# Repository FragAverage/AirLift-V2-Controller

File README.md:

# AirLift V2 Controller

The **AirLift V2 Controller** is a man-in-the-middle controller that sits inline
between an **AirLift V2 Controller controller** and the **air-management
manifold**. It **decodes the proprietary 9600-baud LIN-wired protocol**
in both directions, **rewrites frames if required** so a phone or the vehicle can
drive presets and manual air-up/down without ever desyncing the OEM Controller,
and **reads the vehicle CAN bus** for ignition sensing, lock/unlock triggers (like key fob)
and a live pressure broadcast. Everything is configured from a phone over
**Wi-Fi** — no laptop or serial cable needed in the car.

It runs on the same **ESP32 DevKit V1 (WROOM-32)** PCB as the
[MFSW Controller](https://forbes-automotive.com/products/lin-mfsw-controller),
under the Arduino framework, using both hardware UARTs for the two LIN sides and
the ESP32 **TWAI** peripheral for CAN.

> The firmware acts as a relay and only intercepts
> the manifold bus transiently while a command is queued — control always
> returns to the controller automatically.

---

## Features at a Glance

| Feature | Detail |
|---|---|
| Dual-LIN | Dual LIN channels for Controller (UART1) and manifold (UART2) in dedicated FreeRTOS tasks |
| AirLift Decoder | Decodes every observed frame: FA/F3 polls & replies, the 17-byte status frame, and the 14-byte format-B pressure broadcast |
| Rewrite-in-flight injection | Presets, manual buttons, mode-switch — with verified checksums; the manifold only ever sees one continuous master, so it can't desync |
| Preset editor | Each of 8 presets stored as a `(frontPsi, rearPsi)` in EEPROM, plus a live **Learn** capture from the Controller to allow the user to learn each preset |
| Auto air-out | On ignition loss, broadcast the configured "air-down" target (preset or manual), hold, then turn off manifold power |
| CAN / TWAI | Powertrain quiet-bus ignition detection **or** Comfort-CAN lock/unlock triggers, plus a ~10 Hz pressure broadcast onto the selected bus |
| SavvyCAN GVRET | Capture/inject CAN over Wi-Fi (TCP 23) or USB serial for reverse-engineering |
| Lock/unlock air actions | A double fob-unlock airs the car up; a double fob-lock airs it down (both individually selectable) |
| High-side driver | Powers the controller whenever the vehicle is awake, with configurable CAN silence / min-FPS thresholds |
| Slave display | ~10 Hz ESP-NOW broadcast of pressures / preset / air state to a cluster-mounted CYD display (`SlaveDisplay/`) |
| Wi-Fi UI | Overview, Presets, Settings, Diagnostics, OTA |
| Power management | Auto Wi-Fi-off + CPU reduction 1 minute after the last client disconnects; a fresh CAN burst wakes it back up |
| OTA updates | Flash new firmware from the browser over Wi-Fi |
| EEPROM storage | All settings and presets stored to ESP32 Preferences |

---

### Purchase

The controller runs on the same PCB as the LIN MFSW Controller, available here:
[LIN MFSW Controller — Forbes Automotive](https://forbes-automotive.com/products/lin-mfsw-controller)

---

## Compatibility

Designed for the **AirLift V2** controller + manifold pair that communicate over a
**9600-baud 8N1 LIN-transceiver bus**. The controller is the **bus master** (the
bus is silent when it is unplugged). Frame formats, button codes and checksums
in [`include/defs.h`](include/defs.h) were reverse-engineered from live Saleae
captures (see [`Documents/`](Documents/)) — treat them as a known-good baseline
and re-verify against your own hardware before relying on any injected output.

CAN frame IDs (Comfort fob, broadcast) are **VW PQ-specific** and configurable.

---

## Hardware Overview

### External Interfaces

| Function | Part / circuit |
| --- | --- |
| Controller LIN (LIN 1) | LIN transceiver on `Serial1`, 9600 8N1 — the controller is the master, this device relays it |
| Manifold LIN (LIN 2) | LIN transceiver on `Serial2`, 9600 8N1 — the manifold is the slave |
| CAN | ESP32 TWAI + transceiver (TJA1050 / SN65HVD230); 500 kbit/s Powertrain or 100 kbit/s Comfort |
| Ignition sense (aux) | Optional 12 V level input on the shared aux pin (GPIO 39, input-only) for instant ignition |
| High-side driver | Transistor output (OUTPUT1) supplies +12 V to the controller during ignition-off air-out (5A max.) |

### Pin Map

Defined in [`include/defs.h`](include/defs.h):

| Group | Signal | GPIO |
| --- | --- | --- |
| LIN 1 (Controller) | TX / RX | 17 / 16 |
| LIN 2 (manifold) | TX / RX | 23 / 22 |
| LIN transceivers | Wake / CS-EN | 18 / 19 |
| CAN / TWAI | RX / TX | 13 / 14 |
| Ignition sense | Aux input (input-only pin) | 39 |
| High-side driver | Controller +12 V ("PNP") | 21 |

UARTs are 9600 8N1; CAN is 500 kbit/s (Powertrain) or 100 kbit/s (Comfort).

### Main Connector

The device breaks out to a single 12-way **MX23A12NF1** connector (shared PCB
with the MFSW controller):

> Viewed into the mating face: the top row runs pin **1** (right) to pin **6**
> (left), and the bottom row runs pin **7** (right) to pin **12** (left).

| Pin | Signal | AirLift use |
| --- | --- | --- |
| 1 | `PWR_IN` | 12 V switched / ignition supply |
| 2 | `GND` | Ground |
| 3 | `LIN1` | Controller LIN bus |
| 4 | `LIN2` | Manifold LIN bus |
| 5 | `CHASSIS_CANH` | CAN high |
| 6 | `CHASSIS_CANL` | CAN low |
| 7 | `ANALOG_LIGHT_IN` | Optional ignition-sense input (aux) |
| 8 | `RA` | Unused (resistive output not populated) |
| 9 | `5V` | 5 V rail — typically not required |
| 10 | `OUTPUT1` | Controller +12 V high-side driver |
| 11 | — | Unused |
| 12 | — | Unused |

---

## Jumpers

The shared PCB carries three configuration jumpers:

### LIN1_MASTER

Master pull-up on **LIN 1** (the controller bus). The AirLift Controller provides
the bus master, so this jumper is normally **left off** on the adapter — fit it
only if bench-testing without the real Controller attached.

### LIN2_MASTER

Master pull-up on **LIN 2** (the manifold bus). Fit it if the adapter must
provide the master pull-up on the manifold side; remove it if the manifold
harness already supplies one.

### R_TERM1

The **CAN bus termination resistor**. If this is the only device on the CAN
network leave it fitted; if the vehicle bus is already terminated, remove it.

---

## How It Works

The two LIN sides and the CAN bus each run in dedicated FreeRTOS tasks. The
firmware never seizes the manifold bus outright — the real Controller keeps
polling at its own rate and the firmware simply **rewrites those
frames as they pass through**. Because the manifold only ever sees one
continuous, correctly framed master it can never desync.

```
Controller LIN (master)                Manifold LIN (slave)              Vehicle CAN
        │                                   ▲                              │
        ▼ ControllerToManifoldTask (core 1)   │ manifoldToControllerTask       ▼ ignitionTask (core 0)
 parse poll / button ────────────┐          │ (core 1)                pollCanRx()
        │                        │          │  parse status/pressure       │
   RESTING: byte relay ──────────┼──────────┘  RESTING: byte relay         ▼ switch(id):
        │                        │          ▲       │                 Comfort 0x291 → lock/unlock
   COMMAND: drop poll,           │          │       ▼                       │
   drive manifold ~20 Hz ────────┘   rewrite reply, credit-gated       air-up / air-down queue
        (transformControllerFrame)      relay back to Controller                │
                                                                            ▼ canBroadcastTick()
                                                                     8-byte pressure frame (~10 Hz)
```

### Resting vs. Command

- **Resting** (the default) is a real-time byte-for-byte relay in both
  directions. Both channels still parse a side-channel copy of the traffic, so
  pressures, mode and button state stay live without slowing the bus.
- **Command** (a queued web/CAN action) drops the Controller's messages and drives the manifold at the OEM's active ~20 Hz rate. 

### Air-up / Air-down Triggers

| Source | Action |
| --- | --- |
| Web UI preset / manual buttons | Queue a preset target or manual corner move |
| Ignition loss (`airOutOnIgnOff`) | Broadcast the configured air-down target, hold, drop Controller power |
| Comfort-CAN **double unlock** (`airUpOnFobDouble`) | Air up to the configured preset / PSI |
| Comfort-CAN **double lock** (`airDownOnFobDouble`) | Air down to the configured preset / PSI |

Manual-target moves are closed-loop: the firmware pulses the matching corner
button until the measured axle PSI reaches the target (within tolerance) or the
60s timeout expires.  This may need adjustment(!).

---

## LIN Protocol (Reverse-Engineered)

### Format A — FA-framed polls and replies

```
FA  <payload bytes>  F3
```

**Controller → Manifold (master polls)**

| Bytes                                          | Meaning                              |
|------------------------------------------------|--------------------------------------|
| `01 00 05`                                     | idle poll                            |
| `01 41 XX YY`                                  | MANUAL-mode button event, `YY = (0xC4 - XX) & 0xFF` |
| `01 14 40 00 00 00 B1`                         | PRESET-mode entry poll (state `0x40`, one-shot) |
| `01 14 43 00 00 00 AE`                         | PRESET-mode steady poll (state `0x43`) |
| `01 16 47 TL TR 0F TL TR CHK`                  | preset target broadcast; `TL`/`TR` = front/rear PSI × 2 |

**Manifold → Controller (slave replies)**

| Bytes              | Meaning                          |
|--------------------|----------------------------------|
| `10 F1 00 05`      | idle reply                       |
| `10 F1 04 01`      | reply, MANUAL mode               |
| `10 F1 01 04`      | reply, PRESET mode               |
| `10 0E 00 25 …`    | 17-byte status frame (see below) |

### Manual Button Codes (`01 41 XX YY`, payload[2])

Upper nibble = axle (5 = front, 6 = rear); lower nibble = one-hot bit per
(side, direction): bit0 = L-UP, bit1 = L-DOWN, bit2 = R-UP, bit3 = R-DOWN.

| Code | Button       |  | Code | Button         |
|------|--------------|--|------|----------------|
| 0x51 | FL_UP        |  | 0x61 | RL_UP          |
| 0x52 | FL_DOWN      |  | 0x62 | RL_DOWN        |
| 0x54 | FR_UP        |  | 0x64 | RR_UP          |
| 0x58 | FR_DOWN      |  | 0x68 | RR_DOWN        |
| 0x00 | release/idle |  | 0x80 | MODE_SWITCH (press+hold 1+5) |

Checksum: payload[3] = `(0xC4 - code) & 0xFF`.

### Format A — 17-byte status frame (Manifold → Controller)

```
FA 10 0E 00 MS  FL  RL  FR  RR  TANK  C8 00 00 00 33 00 CHK F3
```

- `payload[3]` = mode/compressor flags: bit5 (`0x20`) heartbeat, bit4 (`0x10`)
  poll-parity, bits0+2 (`0x05`) both set if the compressor is running.
- `payload[5..8]` = FL, RL, FR, RR raw PSI (× 1, **not** × 2).
- `payload[9]`    = tank raw PSI.
- `payload[16]`   = sum-checksum: `(0xFA + Σpayload[0..15] + chk) mod 256 == 0`.

### Format B — 14-byte pressure broadcast (idle-terminated, no FA/F3)

```
00 0A E6 7E   C8 00 4A 00   FL  FR  RL  RR  b12 b13
```

Pressure bytes are PSI × 2. Frame is terminated by ≥4 ms of bus silence
(`kFrameIdleMs`). Kept as a secondary pressure source; format-A status is
preferred when available.

> **Pressure Refresh Rate.** In resting mode pressures are parsed on
> *every* frame the manifold emits, so the on-device values are always as fresh
> as the bus allows. The dashboard now polls `/api/status` at 4 Hz (250 ms).
> The underlying rate is set by how often the manifold chooses
> to broadcast

---

## CAN / TWAI

- **Listen-only** by default; reset to NORMAL mode only when *CAN Broadcast* or
  SavvyCAN transmit is enabled, so the firmware never emits ACK/error bits onto
  a bus while just monitoring.
- Re-initialised in [`src/CAN.cpp`](src/CAN.cpp) (`canReinit()`) when the
  enable flag, ID or bus rate changes via `/api/settings`.

### CAN Source

Exactly one CAN bus is active at a time (a single TWAI controller can only run
at one bit-rate):

- **Powertrain CAN** (500 kbit/s, default) — quiet-bus / minimum-FPS ignition
  detection. Presence is decided by combined activity: silence longer than
  `canSilSec` (default 10 s) **and** frame rate below `canMinFps` (default 50) →
  ignition OFF.
- **Comfort CAN** (100 kbit/s) — parses lock/unlock. `pollCanRx()` feeds each
  frame to a simple `switch (frame.identifier)` case statement; the Comfort fob
  frame (`0x291`, byte 0 = `0x4B` unlock / `0x8B` lock) sets the lock state, and
  a **double** press within 5s queues the configured air-up (unlock) or
  air-down (lock) action.

### Lock/Unlock → Air-Up/Down 

```
Comfort frame 0x291 → canProcessFrame() switch → unlock/lock + double-press detect
                                              → comfortFobDoubleUnlock / …Lock flag
ignitionTask → sees flag → queueTarget(air-up | air-down) → manifold drive
```

### Pressure Broadcast (firmware → vehicle bus)

~10 Hz (`kCanBroadcastPeriodMs = 100`), user-configured 11-bit ID (default
`0x520`), DLC 8:

```
[0] FL PSI*2   [1] FR PSI*2   [2] RL PSI*2   [3] RR PSI*2   [4] Tank PSI*2
[5] flags: bit0 compOn | bit1 ignOn | bit2 intercept | bit3 passthru
          | bits4-5 mode (0=unknown,1=manual,2=preset)
[6] seq counter (free-running)   [7] reserved (0)
```

### Slave Display Broadcast (firmware → ESP-NOW)

A one-way ~10 Hz (`kEspNowPeriodMs = 100`) broadcast to `FF:FF:FF:FF:FF:FF` of
the 24-byte `AirLiftData` struct in `include/airlift_espnow.h` — the receiving
end is the cluster display in **`SlaveDisplay/`**. Broadcast means no pairing and
no knowledge of the display's MAC; nothing is ever received.

```
float fl, fr, rl, rr, tank   // PSI
uint8 preset                 // 1-8 active preset, 0 = none
uint8 status                 // 0 idle, 1 raising, 2 lowering, 3 no signal
```

The struct must stay **byte-identical** to `SlaveDisplay/include/airlift_espnow.h`
(a `static_assert` on both sides guards the size; the receiver can only check the
length, not the field layout).

Two things the LIN wire does not carry directly, so the firmware derives them:

- **Active preset** — the wire has no preset index, only the target pressures
  from `01 16 47`. Those are matched back against the configured/learned preset
  table, which is the same mapping the UI's preset list uses. No match, or not in
  PRESET mode, sends `0` and the display shows `---`.
- **Raising / lowering** — the compressor bit only says the pump is running
  (also true while it refills the tank). Direction comes from a button being held
  right now (ours or the handheld's), and otherwise from the trend of the corner
  pressures, which also covers preset moves where the manifold closed-loops with
  no button held at all.

Because ESP-NOW rides the Wi-Fi radio, the soft-AP channel is pinned to
`kEspNowChannel` (1) to match the display's fixed `ESPNOW_WIFI_CHANNEL`, and the
radio is held up while the broadcast is enabled **and** the ignition is on — see
Power Management below. Toggle in **Settings → Slave Display (ESP-NOW)**.

### SavvyCAN

Enable one setting in **Settings → SavvyCAN**:

- **Wi-Fi GVRET**: connect SavvyCAN to `192.168.1.1:23` as a GVRET network device.
- **Serial GVRET**: connect SavvyCAN to the USB serial port at `1,000,000` baud.

All received frames are forwarded through a queue; SavvyCAN transmit
requests are sent to the vehicle bus while either transport is active.

---

## Power Management

The firmware bundles the universal `power_manager` module used across the
projects. Power state follows the **Wi-Fi client count**, and CAN traffic is the
**wake source** — matching the "sleep when idle, wake when you return to the car"
behaviour:

1. **Boot** — Wi-Fi AP is up and full power.
2. **Idle** — **1 minute after the last Wi-Fi client disconnects**, the module
   turns the WiFi off, drops the CPU 240 MHz → 80 MHz, and clears any web
   override so the controller rests as a pure pass-through. This happens even while the
   car is running (CAN active), keeping the linear regulator cool.
3. **Wake** — while reduced, the TWAI controller keeps receiving (we never
   light-sleep, so no wake interrupt is needed — `ignitionTask` drains the RX
   FIFO every 100 ms). When the bus goes from **quiet → active** and a genuine
   **burst of ≥ `kCanWakeFrameMin` (8) frames** arrives, the board wakes and
   rebuilds the AP for the idle window. It sleeps again 1 minute later if no
   client connected.

> With the ESP-NOW slave display enabled, the radio is **held up while the
> ignition is on** — a cluster gauge that goes blank a minute into a drive is
> worse than the regulator heat it saves. Ignition off (car parked, display
> unpowered) reduces exactly as described above. Turn the broadcast off in
> Settings to restore the old behaviour in full.

> Lock/unlock parsing and air-up/down run in `ignitionTask` and are **independent
> of Wi-Fi** — a fob double-unlock airs the car up whether or not the WiFi is
> awake. The wake-on-burst only restores the web UI.

| Action | Saving |
| --- | --- |
| Wi-Fi off | ~80–120 mA average (single biggest) |
| CPU 240 MHz → 80 MHz | Moderate reduction in active current |
| Bluetooth controller released at boot | ~60 KB RAM freed; small idle saving |
| Onboard LED off at boot | Tiny but persistent saving |

A single stray CAN frame will **not** wake the AP, and a continuous stream that
started while awake will **not** re-wake it after it sleeps — only a fresh
quiet-to-active burst does. An ignition power-cycle always brings Wi-Fi back.

---

## Wi-Fi & Web Interface

Connect to the **`AirLift-V2 Controller`** Wi-Fi access point and browse to
**`http://192.168.1.1/`**. All changed settings are saved automatically.

| Tab | Purpose |
| --- | --- |
| **Overview** | Live FL/FR/RL/RR/Tank PSI, compressor LED, mode, press-and-hold corner buttons (Pointer Events with a safety release), and bus health |
| **Presets** | 8 named buttons + inline `(frontPsi, rearPsi)` editor |
| **Settings** | Pass-through, intercept, air-out-on-ignition-off, air-up/down on fob double-press, CAN source + silence/min-FPS, CAN broadcast ID, SavvyCAN |
| **Diagnostics** | High-side driver override, bus counters, CAN broadcast sent/errors |
| **OTA** | Upload a firmware `.bin` over Wi-Fi and reboot |

### Learn Mode

Enable a preset slot in the UI, then press the matching physical preset on the
Controller: the next `01 16 47 …` target broadcast on the wire is captured into
that slot (the wire carries no preset index, so the slot is bound to the button
you press). Learn windows time-out after a few seconds.

---

### Frame Builders

| Function                                            | Output                                     |
|-----------------------------------------------------|--------------------------------------------|
| `buildIdlePoll(out)`                                | `FA 01 00 05 F3`                           |
| `buildManualButtonPoll(code, out)`                  | `FA 01 41 XX (0xC4-XX) F3`                 |
| `buildPresetTargetPoll(frontPsi, rearPsi, out)`     | `FA 01 16 47 TL TR 0F TL TR CHK F3`        |
| `buildEnterManualPoll(out)` / `buildEnterPresetPoll(out)` | mode-switch / preset-entry polls     |

---

## Configuration

### Feature Flags

Serial debug is defined at the top of [`include/defs.h`](include/defs.h). Set `enableDebug 0` to turn off
everything in one place.  With it on, flip individual categories to focus on a
subsystem. Each category is ANDed with `enableDebug`, and every line is
auto-tagged (e.g. `[CAN]`, `[WiFi]`).

| Flag | Tag | Covers |
| --- | --- | --- |
| `enableDebug` | — | **Master** — `0` disables all serial debug |
| `debugSys` | `[SYS]` | Boot + 1 Hz telemetry |
| `debugPower` | `[PWR]` | Reduced-power / wake (power_manager) |
| `debugWifi` | `[WiFi]` | Soft-AP bring-up |
| `debugIO` | `[IO]` | High-side / controller power / UART init |
| `debugCAN` | `[CAN]` | TWAI driver, vehicle CAN, fob, wake-burst |
| `debugLIN` | `[LIN]` | AirLift LIN MITM (wire / mode / buttons) |
| `debugAPI` | `[API]` | REST / settings / OTA |
| `debugSavvy` | `[SAVVY]` | SavvyCAN GVRET control |

> Serial runs at `serialDebugBaud` (115200). Note: enabling **SavvyCAN Serial
> GVRET** takes over the USB UART at 1 Mbaud, so serial debug and serial GVRET
> are mutually exclusive.

### Key Defaults

| Setting | Default |
| --- | --- |
| LIN Baud | 9600 8N1 |
| CAN Source | Powertrain (500 kbit/s) |
| CAN Silence / min-FPS | 10 s / 50 fps |
| CAN Broadcast ID | `0x520` (disabled by default) |
| Comfort Fob ID / Unlock / Lock | `0x291` / `0x4B` / `0x8B` |
| Fob Double-press Window | 5 s |
| Wi-Fi Idle Timeout | 60 s (after last client) |
| CAN Wake-burst Minimum | 8 frames |
| Wi-Fi AP / IP | `AirLift-V2 Controller` / `192.168.1.1` |
| Pass-through Mode | ON (safe boot default) |

Settings persist to ESP32 Preferences (EEPROM)

---

## Version History

```
V1.00 — ESP32 rewrite: dual-UART rewrite-in-flight MITM, Wi-Fi UI, preset editor.
V2.01 — CAN/TWAI bridge (Powertrain/Comfort), pressure broadcast, SavvyCAN GVRET.
V2.10 — power management (Wi-Fi-client idle + CAN wake-on-burst),
        deferred WiFi bring-up on wake, high-side auto-release, fob boot-delay,
        command-mode idle masking, and single-master gated serial debug.
V2.11 — ESP-NOW broadcast to the slave cluster display, AP channel pinned,
        radio held up while the ignition is on.
```

---

## Disclaimer

Forbes Automotive accepts no responsibility for any incidents arising from the
use of this adapter. Frame IDs, button codes and calibration are vehicle- and
hardware-specific — verify against your own setup before relying on any injected
output or automatic air action.

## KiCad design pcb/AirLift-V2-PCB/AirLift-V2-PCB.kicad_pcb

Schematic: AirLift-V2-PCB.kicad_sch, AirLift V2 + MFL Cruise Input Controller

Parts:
C16: 100nF; C_0805_2012Metric
C_33IN, C_33OUT1: 100nF; C_0805_2012Metric
C_33OUT2: 10uF; C_1206_3216Metric
C_BAT1A, C_BAT2A: 10uF; C_1206_3216Metric
C_BAT1B, C_BAT2B: 100nF; C_0805_2012Metric
C_BULK: 100uF; CP_Radial_D8.0mm_P3.50mm
C_CANV1: 100nF; C_0805_2012Metric
C_CANV2: 1uF; C_1206_3216Metric
C_LINF1, C_LINF2: 1nF; C_0805_2012Metric
C_REGIN1: 100nF; C_0805_2012Metric
C_REGIN2: 10uF; C_1206_3216Metric
C_REGOUT1: 100nF; C_0805_2012Metric
C_REGOUT2: 10uF; C_1206_3216Metric
C_WAKE1, C_WAKE2: 220pF; C_0805_2012Metric
D2: SS34; D_SMA
D3: SMAJ26A; D_SMA
D4, D5: 1N4148; D_SOD-123
D_Z1: BZX84C3V6; SOT-23
J1: MX23A12NF1; MX23A12NF1_2x6_P2.50mm_RA
JP1: LIN1_MASTER; PinHeader_1x02_P2.54mm_Vertical
JP2: LIN2_MASTER; PinHeader_1x02_P2.54mm_Vertical
JP3: R_TERM1; PinHeader_1x02_P2.54mm_Vertical
J_DEVKIT_L: ESP32_DevKit_L; PinSocket_1x15_P2.54mm_Vertical
J_DEVKIT_R: ESP32_DevKit_R; PinSocket_1x15_P2.54mm_Vertical
Q1: IRF4905; TO-220-3_Vertical
Q2: MMBT3904; SOT-23
Q_REV: IRF4905; TO-220-3_Vertical
R1, R6, R7: 1k; R_0805_2012Metric
R2, R4: 4.7k; R_0805_2012Metric
R3, R9: 10k; R_0805_2012Metric
R8: 120; R_0805_2012Metric
R10: 3.3k; R_0805_2012Metric
R_REV: 10k; R_0805_2012Metric
R_RXD1, R_RXD2: 10k; R_0805_2012Metric
U_33: AMS1117-3.3; SOT-223-3_TabPin2
U_CAN: SN65HVD230; SOIC-8_3.9x4.9mm_P1.27mm
U_LIN1, U_LIN2: TJA1020; SOIC-8_3.9x4.9mm_P1.27mm
U_OPTO: PC817; SO-4_7.6x3.6mm_P2.54mm
U_REG: L7805; TO-220-3_Vertical

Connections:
+3V3: C_33OUT1.1, C_33OUT2.1, C_CANV1.1, C_CANV2.1, R2.1, R_RXD1.1, R_RXD2.1, U_33.2 (VO), U_CAN.3 (VCC)
+5V: C_33IN.1, C_REGOUT1.1, C_REGOUT2.1, J1.9, J_DEVKIT_L.15, U_33.3 (VI), U_REG.3 (OUT)
+12V_PROT: C_BAT1A.1, C_BAT1B.1, C_BAT2A.1, C_BAT2B.1, C_BULK.1, C_REGIN1.1, C_REGIN2.1, D2.1 (K), Q1.3 (S), Q_REV.3 (S), R3.1, R6.1, R7.1, U_LIN1.7 (BAT), U_LIN2.7 (BAT), U_REG.1 (IN)
ANALOG_LIGHT_IN: J1.7, R9.1
CAN_RX: J_DEVKIT_L.13, U_CAN.4 (R)
CAN_TERM_A: JP3.1, R8.2
CAN_TX: J_DEVKIT_L.11, U_CAN.1 (D)
CHASSIS_CANH: J1.5, R8.1, U_CAN.7 (CANH)
CHASSIS_CANL: J1.6, JP3.2, U_CAN.6 (CANL)
GND: C16.2, C_33IN.2, C_33OUT1.2, C_33OUT2.2, C_BAT1A.2, C_BAT1B.2, C_BAT2A.2, C_BAT2B.2, C_BULK.2, C_CANV1.2, C_CANV2.2, C_LINF1.2, C_LINF2.2, C_REGIN1.2, C_REGIN2.2, C_REGOUT1.2, C_REGOUT2.2, C_WAKE1.2, C_WAKE2.2, D3.2 (A2), D_Z1.1 (A), J1.2, J_DEVKIT_L.14, J_DEVKIT_R.6, Q2.2 (E), R10.2, R_REV.2, U_33.1 (GND), U_CAN.2 (GND), U_CAN.8 (Rs), U_LIN1.5 (GND), U_LIN2.5 (GND), U_OPTO.2, U_OPTO.3, U_REG.2 (GND)
HSD_BASE: Q2.1 (B), R4.2
HSD_CTRL: J_DEVKIT_R.5, R4.1
HSD_GATE: Q1.1 (G), Q2.3 (C), R3.2
IGN_SENSE: C16.1, D_Z1.3 (K), J_DEVKIT_L.3, R9.2, R10.1
LIN1: C_LINF1.1, J1.3, JP1.2, U_LIN1.6 (LIN)
LIN1_MPU_A: D4.2 (A), R6.2
LIN1_MPU_B: D4.1 (K), JP1.1
LIN1_RX: J_DEVKIT_R.11, R_RXD1.2, U_LIN1.1 (RXD)
LIN1_TX: J_DEVKIT_R.10, U_LIN1.4 (TXD)
LIN2: C_LINF2.1, J1.4, JP2.2, U_LIN2.6 (LIN)
LIN2_MPU_A: D5.2 (A), R7.2
LIN2_MPU_B: D5.1 (K), JP2.1
LIN2_RX: J_DEVKIT_R.2, R_RXD2.2, U_LIN2.1 (RXD)
LIN2_TX: J_DEVKIT_R.1, U_LIN2.4 (TXD)
LIN_NSLP: J_DEVKIT_R.7, U_LIN1.2 (NSLP), U_LIN2.2 (NSLP)
LIN_WAKE: C_WAKE1.1, C_WAKE2.1, J_DEVKIT_R.8, U_LIN1.3 (NWAKE), U_LIN2.3 (NWAKE)
MFL_IN: J_DEVKIT_L.4, R2.2, U_OPTO.4
MFL_LED_A: R1.2, U_OPTO.1
MFL_SIGNAL: D3.1 (A1), J1.11, R1.1
OUTPUT1: D2.2 (A), J1.10, Q1.2 (D)
PWR_IN: J1.1, Q_REV.2 (D)
REV_GATE: Q_REV.1 (G), R_REV.1

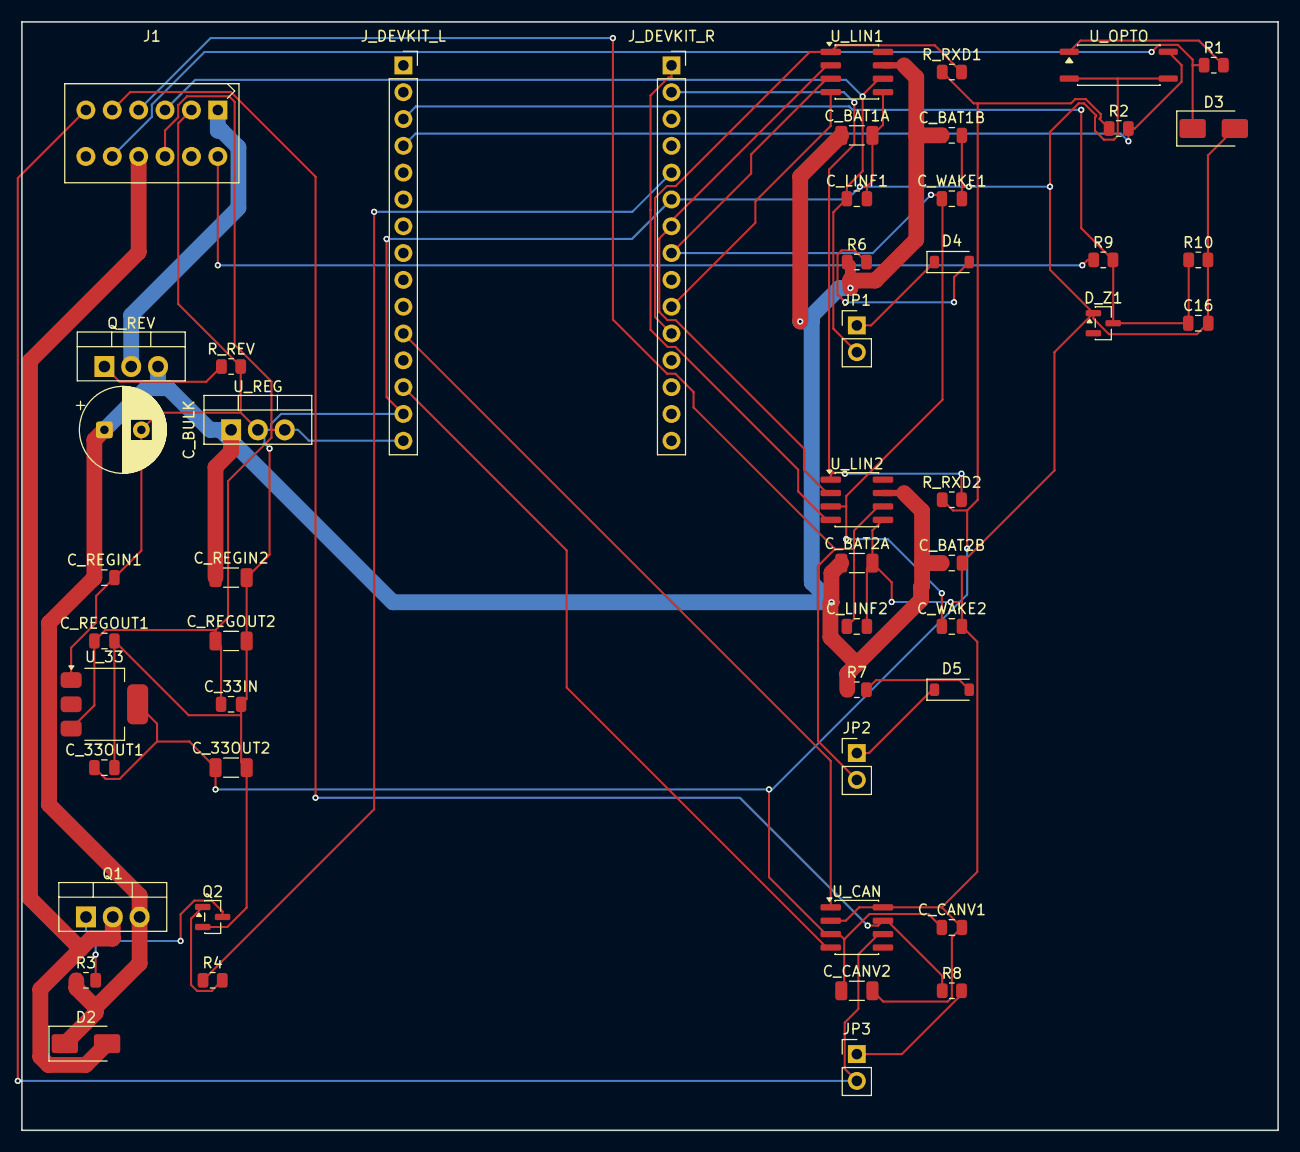
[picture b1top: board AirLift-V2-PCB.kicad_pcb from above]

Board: 2 copper layers, 119.0 x 105.0 mm, 51 parts (0 on the bottom side), 32 nets.

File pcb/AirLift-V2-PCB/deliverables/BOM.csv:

"Reference","Value","Footprint","Datasheet"
"C16","100nF","Capacitor_SMD:C_0805_2012Metric",""
"C_33IN?","100nF","Capacitor_SMD:C_0805_2012Metric",""
"C_33OUT1","100nF","Capacitor_SMD:C_0805_2012Metric",""
"C_33OUT2","10uF","Capacitor_SMD:C_1206_3216Metric",""
"C_BAT1A?","10uF","Capacitor_SMD:C_1206_3216Metric",""
"C_BAT1B?","100nF","Capacitor_SMD:C_0805_2012Metric",""
"C_BAT2A?","10uF","Capacitor_SMD:C_1206_3216Metric",""
"C_BAT2B?","100nF","Capacitor_SMD:C_0805_2012Metric",""
"C_BULK?","100uF","Capacitor_THT:CP_Radial_D8.0mm_P3.50mm",""
"C_CANV1","100nF","Capacitor_SMD:C_0805_2012Metric",""
"C_CANV2","1uF","Capacitor_SMD:C_1206_3216Metric",""
"C_LINF1","1nF","Capacitor_SMD:C_0805_2012Metric",""
"C_LINF2","1nF","Capacitor_SMD:C_0805_2012Metric",""
"C_REGIN1","100nF","Capacitor_SMD:C_0805_2012Metric",""
"C_REGIN2","10uF","Capacitor_SMD:C_1206_3216Metric",""
"C_REGOUT1","100nF","Capacitor_SMD:C_0805_2012Metric",""
"C_REGOUT2","10uF","Capacitor_SMD:C_1206_3216Metric",""
"C_WAKE1","220pF","Capacitor_SMD:C_0805_2012Metric",""
"C_WAKE2","220pF","Capacitor_SMD:C_0805_2012Metric",""
"D2","SS34","Diode_SMD:D_SMA",""
"D3","SMAJ26A","Diode_SMD:D_SMA",""
"D4","1N4148","Diode_SMD:D_SOD-123",""
"D5","1N4148","Diode_SMD:D_SOD-123",""
"D_Z1","BZX84C3V6","Package_TO_SOT_SMD:SOT-23",""
"J1","MX23A12NF1","AirLift_Custom:MX23A12NF1_2x6_P2.50mm_RA",""
"JP1","LIN1_MASTER","Connector_PinHeader_2.54mm:PinHeader_1x02_P2.54mm_Vertical",""
"JP2","LIN2_MASTER","Connector_PinHeader_2.54mm:PinHeader_1x02_P2.54mm_Vertical",""
"JP3","R_TERM1","Connector_PinHeader_2.54mm:PinHeader_1x02_P2.54mm_Vertical",""
"J_DEVKIT_L?","ESP32_DevKit_L","Connector_PinSocket_2.54mm:PinSocket_1x15_P2.54mm_Vertical",""
"J_DEVKIT_R?","ESP32_DevKit_R","Connector_PinSocket_2.54mm:PinSocket_1x15_P2.54mm_Vertical",""
"Q1","IRF4905","Package_TO_SOT_THT:TO-220-3_Vertical",""
"Q2","MMBT3904","Package_TO_SOT_SMD:SOT-23",""
"Q_REV?","IRF4905","Package_TO_SOT_THT:TO-220-3_Vertical",""
"R1","1k","Resistor_SMD:R_0805_2012Metric",""
"R2","4.7k","Resistor_SMD:R_0805_2012Metric",""
"R3","10k","Resistor_SMD:R_0805_2012Metric",""
"R4","4.7k","Resistor_SMD:R_0805_2012Metric",""
"R6","1k","Resistor_SMD:R_0805_2012Metric",""
"R7","1k","Resistor_SMD:R_0805_2012Metric",""
"R8","120","Resistor_SMD:R_0805_2012Metric",""
"R9","10k","Resistor_SMD:R_0805_2012Metric",""
"R10","3.3k","Resistor_SMD:R_0805_2012Metric",""
"R_REV?","10k","Resistor_SMD:R_0805_2012Metric",""
"R_RXD1","10k","Resistor_SMD:R_0805_2012Metric",""
"R_RXD2","10k","Resistor_SMD:R_0805_2012Metric",""
"U_33","AMS1117-3.3","Package_TO_SOT_SMD:SOT-223-3_TabPin2",""
"U_CAN?","SN65HVD230","Package_SO:SOIC-8_3.9x4.9mm_P1.27mm",""
"U_LIN1","TJA1020","Package_SO:SOIC-8_3.9x4.9mm_P1.27mm",""
"U_LIN2","TJA1020","Package_SO:SOIC-8_3.9x4.9mm_P1.27mm",""
"U_OPTO?","PC817","Package_SO:SO-4_7.6x3.6mm_P2.54mm",""
"U_REG?","L7805","Package_TO_SOT_THT:TO-220-3_Vertical",""
